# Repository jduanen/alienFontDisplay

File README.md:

# alienFontDisplay
Display made of six eight-segment EL display units with per-display custom driver board and controller.

Scrolling display board that displays whatever string is published on a given MQTT channel over WiFi.

These displays were used in Russian tanks and missile launch consoles.

## TBD
* Design 225VAC 400Hz inverter that can supply ?mA (?W)
* BOM
* WiFi interface board
* Firmware
* Tests
* Example code
* Documentation

### Display Pinout

### Alphanumeric Font

### Single Display and Driver Board

### Driver PCB

### Schematic

# EL Displays

## IEL-O-VI C63.396.208-02
* Blue, Alien Font, Russian/Soviet Electroluminescent Display
* [0-9] and [A-Z] (after a fashion)
  - some characters are lower case and some are missing strokes
    * in particular, there isn't a center vertical stroke, so "T" and "I" are not so great
  - seems to have been designed for Cyrillic characters
* pinout
  - 1: common
  - 2: bottom horizontal (S)
  - 3: bottom right angled (M)
  - 5: n/c?
  - 7: left vertical (L)
  - 8: bottom left angled (M)
  - 11: top right angled (M)
  - 14: left vertical (L)
  - 17: top horizontal (S)
  - 20: top left angled (M)
* per-segment capacitance (estimates)
  - S (2x): 55 pFd
  - M (4x): 90 pFd
  - L (2x): 170 pFd

# Power Supply Design

* Specs
  - 220VAC @ 400Hz
  - 0.5-3mA per display
    * four displays: 12mA (max)
    * six displays: 18mA (max)
* Design alternatives
  - drive audio amp into (CT?) step-up transformer
  - DC boost converter into H-Bridge

=========================

* notes
  - ~200V @ 400Hz
  - not squarewave -- filter or triangle wave for constant dv/dt
  - less bright at 50Hz, but last longer
  - need current limiting resistor if power source has low internal resistance
    * e.g., 330K ohm @ 220V @ 50Hz
  - 500 Hrs lifespan
  - sine/square voltage up to 250V and 400Hz-5KHz
  - decay time fractions of msec
  - at least 6usec pulse
  - no loss of brightness in pulses of 100usec at constant duty cycle
  - most of drop in brightness occurs in first 200 hours of operation
    * relatively flat after that
  - for best lifetime, maintain constant frequency and reduce voltage
  - use current limiting resistor for supplies with internal resistance less than 1Kohm
  - add 0.03-0.05ufd caps in parallel with electrodes to improve reliability
  - nomenclature
    * I: indicator
    * EL: electroluminescent
    * color
      - O: one color
      - M: multicolor
      - P: raster
    * size (13x sizes)
      - VI: 34x40mm
      - II: 13x35mm
      - IV: 18x26mm
      - 
    * number of dots indicate brightness
  - IEL-0-VI-101-246: 19x segment starburst with bar above and left and right commas
  - constant power mode
    * 220V @ 400Hz
  - constant brightness mode
    * 175-250V @ 1200Hz -- increases with service life
  - 0.5-3 mA current
  - DC will destroy the display
  - can't multiplex displays -- need driver for each segment
  - lifetime drops rapidly with supply frequency >400Hz

* Links
  - https://www.nixology.uk/el-displays/
  - http://www.155la3.ru/electroluminescent.htm?fbclid=IwAR3kzInl6R3qaqCM56aDhy-eqRuBEZQ2xA1R94jkRoaB9Y2xDsH_GoB88GI
  - https://www.youtube.com/watch?v=p6mNbgtnFK8
  - http://lampes-et-tubes.info/cd/cd143.php?l=e
  - http://www.nedopc.org/forum/viewtopic.php?f=65&t=11093
  - https://www-nedopc-org.translate.goog/forum/viewtopic.php?f=65&t=11093&_x_tr_sch=http&_x_tr_sl=auto&_x_tr_tl=en&_x_tr_hl=en-US&_x_tr_pto=wapp

* Sparkfun EL Inverter (COM-10469 retired)
  - input: 12VDC
  - output: 70-110V (90V typ)
  - frequency: 800-3500Hz (2000Hz typ)

* Sparkfun EL Inverter (sourced from Amazon)
  - input: 5VDC
  - output: 225VAC (in afd circuit)
  - frequency: 5-7KHz (in afd circuit)

=======================================================================================
* SmartSocket for Alien Font displays
  - use same protocol on daisy-chained 9600 baud RS232 (3v3?)
    * http://tayloredge.com/reference/Circuits/1386SmartSocket/SmartSockets.pdf
  - build single-sided PCB that fits on back of display units
    * drive each segment individually
    * use common HV PSU
    * use circuits from SparkFun boards as they have been tested and shown to work
  - need to select a PIC to use as the on-board controller
    * PIC18F16Q41: same as PIC18F16Q40 but has an opAmp
    * PIC18F16Q40:
      - 14pin device has six GPIOs on PortA and another six on PortC
      - has 1/2 UARTs
      - 64KB program FLASH, 4KB SRAM, 512B EEPROM
      - 18x GPIO, 2/3x 8b timers, 17x channels of 12b ADC, 2x 8b DACs, 4x DMA
      - 32b CRC with scanner, vectored interrupts, temperature indicator, NCO, PWM/CCP
      - C compiler
        * CCS: http://www.ccsinfo.com -- $200-$500
        * Hi-Tech: http://www.htsoft.com -- bought by Microchip
        * Microchip: http://www.microchip.com -- free student mode
        * MPLAB C18: microchip
        * MikroC: free student version with limits
        * https://www.microchip.com/en-us/development-tool/C18
      - $1.5 at Mouser (in stock)
        * PIC18F16Q40-E/SO
        * https://www.mouser.com/ProductDetail/Microchip/PIC18F16Q40-E-SO?qs=sGAEpiMZZMv0NwlthflBi%252BydFA3s6SRqoyEH6IOSDHM%3D
      - example: https://github.com/microchip-pic-avr-examples/pic18f16q40-quadrature-decoder
        * RA2: UART Tx programmer?
        * RB7: UART Tx
        * RB5: UART Rx
        * RB4, RB6, RA4, RA5, RC0-RC7: GPIO
      - PPS re-mappable input signals can be moved from default locations to other ports
        * UART outputs: DTR1, RTS1, TX1, DTR2, RTS2, TX2, DTR3, RTS3, TX3
        * UART inputs: RX1, CTS1, RX2, CTS2, RX3, CTS3 
      - pin allocation table (default)
        * RB5: RX1
        * RB7: CTS1
        * RC1: RX2
        * RC2: CTS2
        * RC3: RX3
        * RC5: CTS3
  - use shift registers?
  - use I2C port expander?

* display unit dimensions, pin and threaded spacer locations are not consistent across instances

* Use SparkFun EL boards for proof of concept testing

* EL Sequencer v23
  - https://www.sparkfun.com/products/12781
  - http://cdn.sparkfun.com/datasheets/Components/EL/SparkFun_EL_Sequencer_v23.pdf
  - ATMega328P processor on-board
    * use "Arduino Duemilanove or Diecimila" board with FTDI USB dongle
  - Gets HV from Sparkfun EL Inverter
    * not ideal -- need higher voltage and better frequency
  - Drives HV to all segments of all displays
    * EL Escudo Dos pulls display commons to HV_GND
  - D2-D9 used to drive EL_A-EL_H
    * EL_A: pin 2
    * EL_B: pin 3
    * EL_C: pin 7
    * EL_D: pin 8
    * EL_E: pin 11
    * EL_F: pin 14
    * EL_G: pin 17
    * EL_H: pin 20
  - Sends six (active high) TTL signals to EL Escudo Dos to enable each display
    * ADC_0 (JP4:2): display #1
    * ADC_1 (JP4:7): display #2
    * ADC_2 (JP2:8): display #3
    * ADC_3 (JP2:7): display #4
    * ADC_4 (JP2:6): display #5
    * ADC_5 (JP2:5): display #6

* EL Escudo Dos
  - https://www.sparkfun.com/products/10878
  - https://cdn.sparkfun.com/datasheets/Components/EL/EL_Escudo_Dos/EL%20Escudo%20Dos%20v21.pdf
  - Pulls display common lines (pin 1) down to HV_GND
  - EL_H: display #1 ... EL_C: display #6
  - gets HV_GND and TTL display unit selector signals from EL Sequencer
  - all SCRs have common HV connected to their tabs
    * and they have individual outputs to load and ground
  - need to cut HV to tabs and connect them to the display common signals
    * and short all load outputs to HV_GND

* misc
  - mqtt listener
    * mosquitto_sub -t /displays/# -F "%I,%t,%p"
  - commands
    * rssi
    * version
    * reset
    * rate[=<rate>]
    * scrollDelay[=<msecs>]
    * pause[=<msecs>]
    * display[=<str>]
  - e.g., mosquitto_pub -t "/displays/afd/<IPAddr>/cmd" -m "display=abcdefghijklmnopqrstuvwxyz0123456789"

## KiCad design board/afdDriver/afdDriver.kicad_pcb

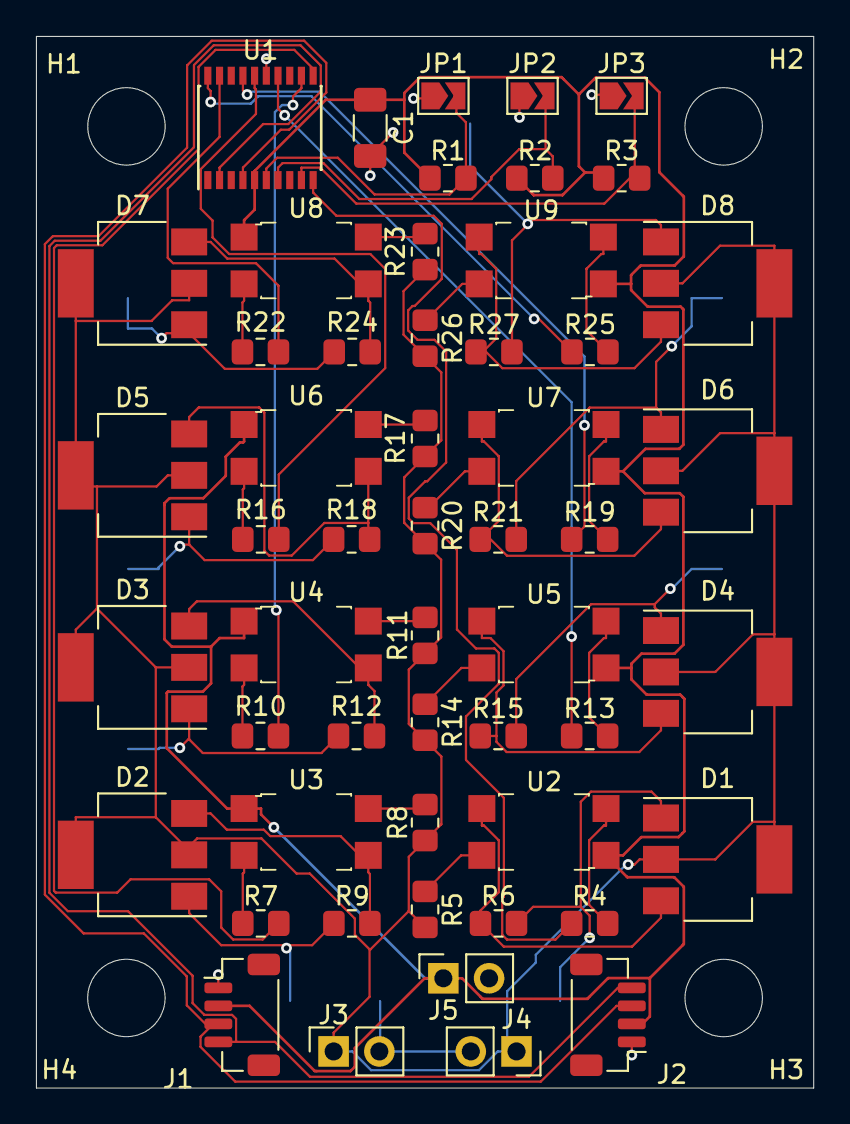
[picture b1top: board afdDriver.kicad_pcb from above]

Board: 2 copper layers, 43.2 x 58.4 mm, 58 parts (1 on the bottom side), 49 nets.

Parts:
C1: 0.1 uFd; C_1206_3216Metric_Pad1.33x1.80mm_HandSolder
D1, D2, D3, D4, D5, D6, D7, D8: Z0103MN; SOT-223
DS1: IEL-O-VI_C63.396.208-02_SMD; C63.396.208-02_SMD
H1, H2, H3, H4: MountingHole; MountingHole_4.3mm_M4_ISO14580
J1, J2: Qwiic_Connector; JST_SH_BM04B-SRSS-TB_1x04-1MP_P1.00mm_Vertical
J3, J4: HighVoltageAC; PinSocket_1x02_P2.54mm_Vertical
J5: Power; PinSocket_1x02_P2.54mm_Vertical
JP1: ADDR0; SolderJumper-2_P1.3mm_Open_TrianglePad1.0x1.5mm
JP2: ADDR1; SolderJumper-2_P1.3mm_Open_TrianglePad1.0x1.5mm
JP3: ADDR2; SolderJumper-2_P1.3mm_Open_TrianglePad1.0x1.5mm
R1, R2, R3: 10K Ohm; R_0805_2012Metric_Pad1.20x1.40mm_HandSolder
R4, R5, R6, R7, R8, R9, R10, R11, R12, R13, R14, R15, R16, R17, R18, R19, R20, R21, R22, R23, R24, R25, R26, R27: 390; R_0805_2012Metric_Pad1.20x1.40mm_HandSolder
U1: PCF8574TS; SSOP-20_4.4x6.5mm_P0.65mm
U2, U3, U4, U5, U6, U7, U8, U9: QTM3063T1; 4-SMD_3.8x4.6mm

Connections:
+5V: C1.1, J1.2, J2.2, J5.1, R1.1, R2.1, R3.1, U1.5, U2.1, U3.1, U4.1, U5.1, U6.1, U7.1, U8.1, U9.1
/A0: JP1.2, R1.2, U1.6
/A1: JP2.2, R2.2, U1.7
/A2: JP3.2, R3.2, U1.9
/EnbSegA: R4.2, U1.10
/EnbSegB: R7.2, U1.11
/EnbSegC: R10.2, U1.12
/EnbSegD: R13.2, U1.14
/EnbSegE: R16.2, U1.16
/EnbSegF: R19.2, U1.17
/EnbSegG: R22.2, U1.19
/EnbSegH: R25.2, U1.20
/SCL: J1.4, J2.4, U1.2
/SDA: J1.3, J2.3, U1.4
/SegA: D1.1, DS1.2, R6.1
/SegB: D2.1, DS1.3, R9.1
/SegC: D3.1, DS1.7, R12.1
/SegD: D4.1, DS1.8, R15.1
/SegE: D5.1, DS1.11, R18.1
/SegF: D6.1, DS1.14, R21.1
/SegG: D7.1, DS1.17, R24.1
/SegH: D8.1, DS1.20, R27.1
GND: C1.2, J1.1, J2.1, J5.2, JP1.1, JP2.1, JP3.1, U1.15
GND1: DS1.1, J3.2, J4.2
HV_AC: D1.2, D1.4, D2.2, D2.4, D3.2, D3.4, D4.2, D4.4, D5.2, D5.4, D6.2, D6.4, D7.2, D7.4, D8.2, D8.4, J3.1, J4.1, R5.1, R8.1, R11.1, R14.1, R17.1, R20.1, R23.1, R26.1
unnamed: D1.3, R6.2, U2.3
unnamed: D2.3, R9.2, U3.3
unnamed: D3.3, R12.2, U4.3
unnamed: D4.3, R15.2, U5.3
unnamed: D5.3, R18.2, U6.3
unnamed: D6.3, R21.2, U7.3
unnamed: D7.3, R24.2, U8.3
unnamed: D8.3, R27.2, U9.3
unnamed: R4.1, U2.2
unnamed: R5.2, U2.4
unnamed: R7.1, U3.2
unnamed: R8.2, U3.4
unnamed: R10.1, U4.2
unnamed: R11.2, U4.4
unnamed: R13.1, U5.2
unnamed: R14.2, U5.4
unnamed: R16.1, U6.2
unnamed: R17.2, U6.4
unnamed: R19.1, U7.2
unnamed: R20.2, U7.4
unnamed: R22.1, U8.2
unnamed: R23.2, U8.4
unnamed: R25.1, U9.2
unnamed: R26.2, U9.4

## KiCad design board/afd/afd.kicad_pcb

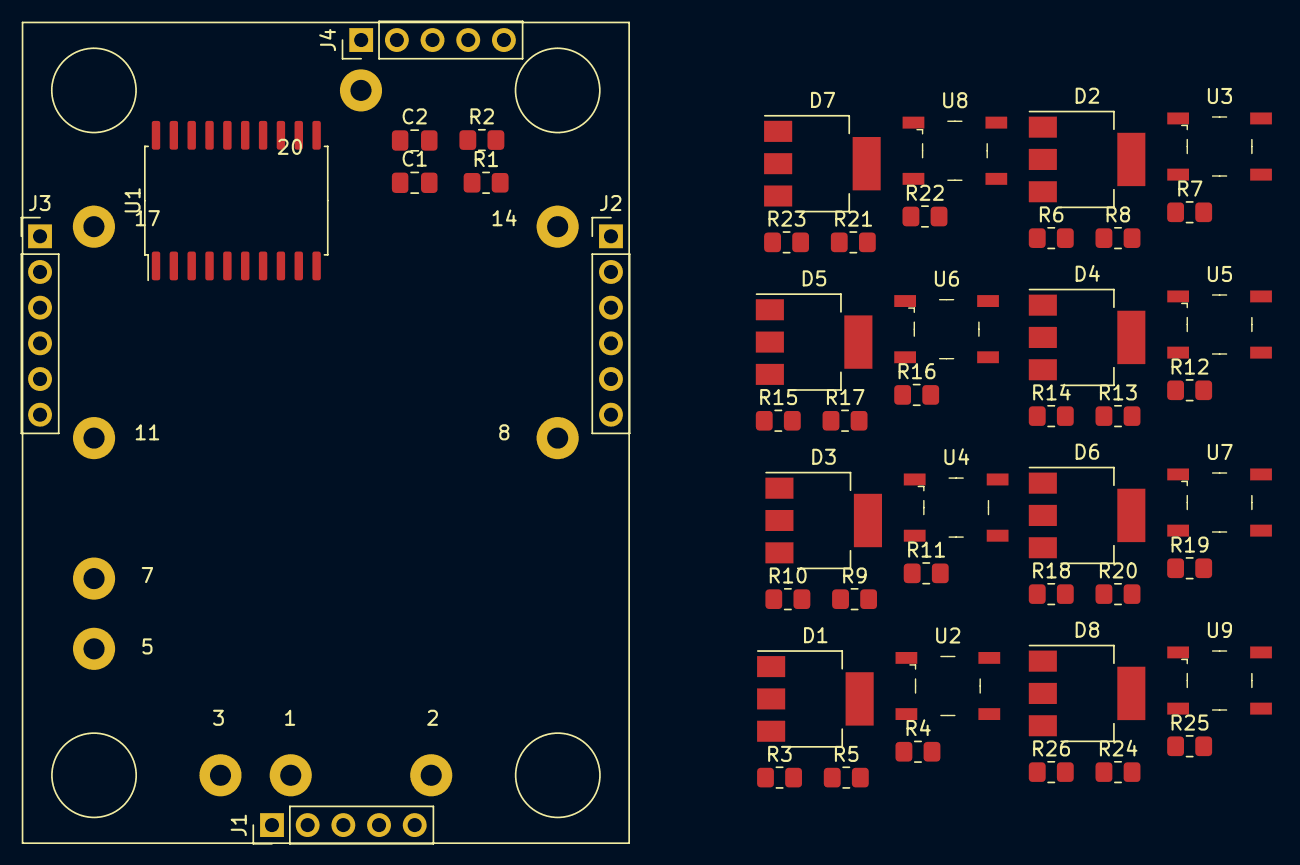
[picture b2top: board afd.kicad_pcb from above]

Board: 2 copper layers, 50 parts (0 on the bottom side), 48 nets, no tracks yet.

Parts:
C1, C2: 0.1 uF 20V ceramic; C_0805_2012Metric_Pad1.18x1.45mm_HandSolder
D1, D2, D3, D4, D5, D6, D7, D8: Z0103MN; SOT-223
DS1: IEL-O-VI_C63.396.208-02; C63.396.208-02
J1: ICSP Connector; PinHeader_1x05_P2.54mm_Vertical
J2: Input Connector; PinHeader_1x06_P2.54mm_Vertical
J3: Output Connector; PinHeader_1x06_P2.54mm_Vertical
J4: GPIO Connector; PinHeader_1x05_P2.54mm_Vertical
R1: 10 Kohm; R_0805_2012Metric_Pad1.20x1.40mm_HandSolder
R2: 470 ohm; R_0805_2012Metric_Pad1.20x1.40mm_HandSolder
R3, R4, R5, R6, R7, R8, R9, R10, R11, R12, R13, R14, R15, R16, R17, R18, R19, R20, R21, R22, R23, R24, R25, R26: 390; R_0805_2012Metric_Pad1.20x1.40mm_HandSolder
U1: PIC18F16Q40-E_SO; SOIC-20W_7.5x12.8mm_P1.27mm
U2, U3, U4, U5, U6, U7, U8, U9: MOC3063; SMD-4_5x4.4mm_P4mm

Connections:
+3V3: C2.1, J1.2, J2.5, J3.5, R1.1, U1.1
/EnbSegA: U1.16, U2.1
/EnbSegB: U1.15, U3.1
/EnbSegC: U1.14, U4.1
/EnbSegD: U1.7, U5.1
/EnbSegE: U1.6, U6.1
/EnbSegF: U1.5, U7.1
/EnbSegG: U1.8, U8.1
/EnbSegH: U1.9, U9.1
/GPIO0: J4.5, U1.17
/GPIO1: J4.4, U1.2
/GPIO2: J4.3, U1.3
/GPIO3: J4.2, U1.11
/GPIO4: J4.1, U1.10
/ICSPCLK: J1.5, U1.18
/ICSPDAT: J1.4, U1.19
/MCLR: R2.1, U1.4
/RX1: J2.3, U1.12
/SegA: D1.1, DS1.2, R5.1
/SegB: D2.1, DS1.3, R8.1
/SegC: D3.1, DS1.7, R11.1
/SegD: D4.1, DS1.8, R14.1
/SegE: D5.1, DS1.11, R17.1
/SegF: D6.1, DS1.14, R20.1
/SegG: D7.1, DS1.17, R23.1
/SegH: D8.1, DS1.20, R26.1
/TX1: J3.3, U1.13
/Vpp: C1.1, J1.1, R1.2, R2.2
GND: C1.2, C2.2, J1.3, J2.6, J3.6, U1.20
GND1: DS1.1, J2.4, J3.4, R3.2, R6.2, R9.2, R12.2, R15.2, R18.2, R21.2, R24.2
HV_AC: D1.2, D1.4, D2.2, D2.4, D3.2, D3.4, D4.2, D4.4, D5.2, D5.4, D6.2, D6.4, D7.2, D7.4, D8.2, D8.4, J2.2, J3.2, R4.1, R7.1, R10.1, R13.1, R16.1, R19.1, R22.1, R25.1
unnamed: D1.3, R5.2, U2.4
unnamed: D2.3, R8.2, U3.4
unnamed: D3.3, R11.2, U4.4
unnamed: D4.3, R14.2, U5.4
unnamed: D5.3, R17.2, U6.4
unnamed: D6.3, R20.2, U7.4
unnamed: D7.3, R23.2, U8.4
unnamed: D8.3, R26.2, U9.4
unnamed: J2.1, J3.1
unnamed: R3.1, U2.2
unnamed: R6.1, U3.2
unnamed: R9.1, U4.2
unnamed: R12.1, U5.2
unnamed: R15.1, U6.2
unnamed: R18.1, U7.2
unnamed: R21.1, U8.2
unnamed: R24.1, U9.2

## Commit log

2021-11-12 Updated.
2021-11-12 Created.
2021-11-12 Added.
2021-11-12 Added char/digit to segment maps.
2021-11-17 Deleted.
2021-11-18 Changed to one segmentDriver sheet.
2021-11-18 Moved.
2021-11-19 Put regulator on root page. Replicated segment driver child page.
2021-11-19 Removed.
2021-11-22 Redrew schematic using labels.
2021-11-22 Fixed DRC errors.
2021-11-23 Checkpoint.
2021-11-23 Before circuit change.
2021-11-23 Removed regulator.
2021-11-23 Final attempt at single board.
2021-11-23 Changed optoisolator to smaller package.
2021-11-25 Added two ground posts.
2021-11-26 Checkpoint. Starting layout.
2021-11-26 Checkpoint. New 3dmodels.
2021-11-26 Renamed.
2021-11-28 Auto-routed.
2021-12-06 Test digits.
2021-12-07 V1.0.0 design.
2021-12-10 Embiggened +5V net.
2021-12-12 Fixed B.Mask text.
2021-12-12 Improved B.Silk layer on PCB. V1.0.1.
2021-12-12 Improved RefDes for DS1 on B.Silk
2022-01-12 Added another test.
2022-01-13 Added another test case.
2022-01-14 Added new test.
2022-01-15 Added writeUnits().
2022-01-15 Started afdPrint().
2022-01-16 First cut.
2022-01-16 First working test version.
2022-01-16 First working version.
2022-01-20 Added get/set methods for maxStrLen and scrollDelay.
2022-01-21 Fixed subscribe problem.
2022-01-21 Made callback work.
2022-01-21 Removed maxStrLen. Added pause between message iterattions.
2022-01-21 Fixed typo in report message.
2022-01-21 Ignore command case. Put RSSI at end of report. Bumped version.
2022-01-21 Added TODO comment.
2022-02-09 Fixed typo.
2022-02-18 Converted to use conditional print.
2022-02-18 Removed 208-1 info.
2022-04-04 Updated to use callback library.

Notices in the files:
board/afdDriver/afdDriver.kicad_pcb:
MIT License
